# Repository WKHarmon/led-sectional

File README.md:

# LED Sectional

A WiFi-connected LED display for aviation sectional maps that shows real-time flight conditions at airports using color-coded LEDs.

## What It Does

The LED Sectional automatically fetches current weather data (METARs) from aviationweather.gov and displays flight conditions on your sectional map:

| Color | Meaning |
|-------|---------|
| Green | VFR - Clear skies, good visibility |
| Blue | MVFR - Marginal conditions |
| Red | IFR - Instrument conditions |
| Magenta | LIFR - Low IFR, poor conditions |
| Yellow | High Winds - VFR with winds over 25 knots |
| White Flash | Thunderstorms reported |
| Off | No data available |

Weather updates automatically every 15 minutes.

## What You Need

### Hardware

- **Controller board** - ESP8266-based (Wemos D1 Mini Lite recommended), or purchase a [pre-made kit](docs/kit.md)
- **LED string** - WS2811 or WS2812 LEDs (one per airport)
- **Power supply** - 5V DC, sized for your LED count
- **USB cable** - For initial setup (must support data, not charge-only)

### Your Map

You'll need a framed sectional chart with holes drilled at each airport location. See the [full build guide](docs/index.md) for detailed instructions on creating your map.

## Setup

### Step 1: Install the Firmware

1. Visit the [LED Sectional Configuration Tool](https://led-sectional.kyleharmon.com/configure/)
2. Connect your controller via USB
3. Click the **Firmware** tab
4. Click **Install Firmware** and follow the prompts

### Step 2: Connect to WiFi

After installing firmware, the controller needs your WiFi credentials:

1. Keep the USB cable connected
2. In the Configuration Tool, click **Connect**
3. Go to the **WiFi** tab
4. Enter your network name and password
5. Click **Save** - the device will reboot and connect

**Note:** The controller only works with 2.4 GHz WiFi networks.

### Step 3: Add Your Airports

1. In the Configuration Tool, go to the **Airports** tab
2. Add airports in order matching your LED string (LED 1 first, LED 2 second, etc.)
3. Use standard ICAO codes (e.g., KSFO, KJFK, KORD)
4. Click **Save** to upload to the device

**Special codes:**
- `NULL` - Skip an LED (leave it off)
- `VFR`, `MVFR`, `IFR`, `LIFR`, `WVFR` - Legend LEDs that always show that color
- `WBNK` - Wind blink demo - alternates between green and yellow (requires "Alternate Colors" setting enabled)

### Step 4: Mount and Enjoy

Disconnect USB, connect your 5V power supply, and mount your sectional!

## Troubleshooting

### LEDs aren't lighting up

- Check that your power supply is 5V and has enough current for your LED count
- Verify the data wire is connected to the correct pin (GPIO 14 / D5 by default)
- Make sure the LED string and controller share a common ground

### Can't connect via Web Serial

- Use Chrome, Edge, or Opera (Safari and Firefox don't support Web Serial)
- Try a different USB cable - some cables only carry power, not data
- Close any other programs that might be using the serial port

### WiFi won't connect

- Confirm your network is 2.4 GHz (5 GHz is not supported)
- Double-check the password
- Move the controller closer to your router during setup

### Some airports show no color

- The airport may not have recent METAR data
- Verify the ICAO code is correct at [aviationweather.gov](https://aviationweather.gov/)

## Adjusting Settings

In the Configuration Tool's **Settings** tab, you can adjust:

- **Brightness** - LED brightness level (0-255)
- **Wind Threshold** - Wind speed that triggers yellow color (default: 25 knots)
- **Lightning Animation** - Enable/disable flashing for thunderstorms
- **High Wind Indication** - Enable/disable yellow for high winds
- **Light Sensor** - Enable automatic brightness based on room lighting (requires additional hardware)

### Home Assistant Integration

The LED Sectional can integrate with Home Assistant for smart home control. Once configured, your sectional appears as a light in Home Assistant where you can:

- Turn the display on/off
- Adjust brightness
- Include in automations (e.g., dim at night, turn off when away)

To set up, go to **Settings > Advanced Settings** in the Configuration Tool and enable MQTT. Enter your Home Assistant's MQTT broker address and credentials. The device will automatically appear in Home Assistant via MQTT Discovery.

## More Information

- [Full Build Guide](docs/index.md) - Detailed instructions for building your sectional
- [Kit Information](docs/kit.md) - Pre-made electronics kit
- [Contributing & Development](CONTRIBUTING.md) - For developers who want to modify the code

## Acknowledgments

- Inspired by [this Reddit post](https://www.reddit.com/r/flying/comments/7avr8q/flight_conditions_sectional_wall_art_thing/) and [Dylan Rush's blog](http://blog.dylanhrush.com/2017/07/live-sectional-map.html)
- Weather data from [aviationweather.gov](https://aviationweather.gov/)
- Web flashing powered by [ESP Web Tools](https://esphome.github.io/esp-web-tools/)

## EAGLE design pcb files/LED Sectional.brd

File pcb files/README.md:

# PCB Files
Originally this project used a WEMOS D1 Mini; however, to make assembly a bit easier the PCB now has all the components placed on the PCB directly, including an ESP8285 microcontroller. All of the SMD components are from the parts library that [jlcpcb.com](https://jlcpcb.com) can assemble directly for cheap. The files in this folder are:

* LED Sectional PCB - EasyEDA.json - PCB design file for import into EasyEDA.
* LED Sectional - Gerbers.zip - PCB production files that should be usable by any PCB manufacturer.
* LED Sectional - BOM.csv - All of the components used in the board design.
* LED Sectional - Centroid.csv - Pick and place file for assembly of the SMD components.

If assembling through jlcpcb.com, it's still necessary to solder all of the through hole components like the micro USB, power, and LED connectors. Other assembly fabs can handle the thru-hole components, but most charge significantly more for the via-in-pads that are used in the design.

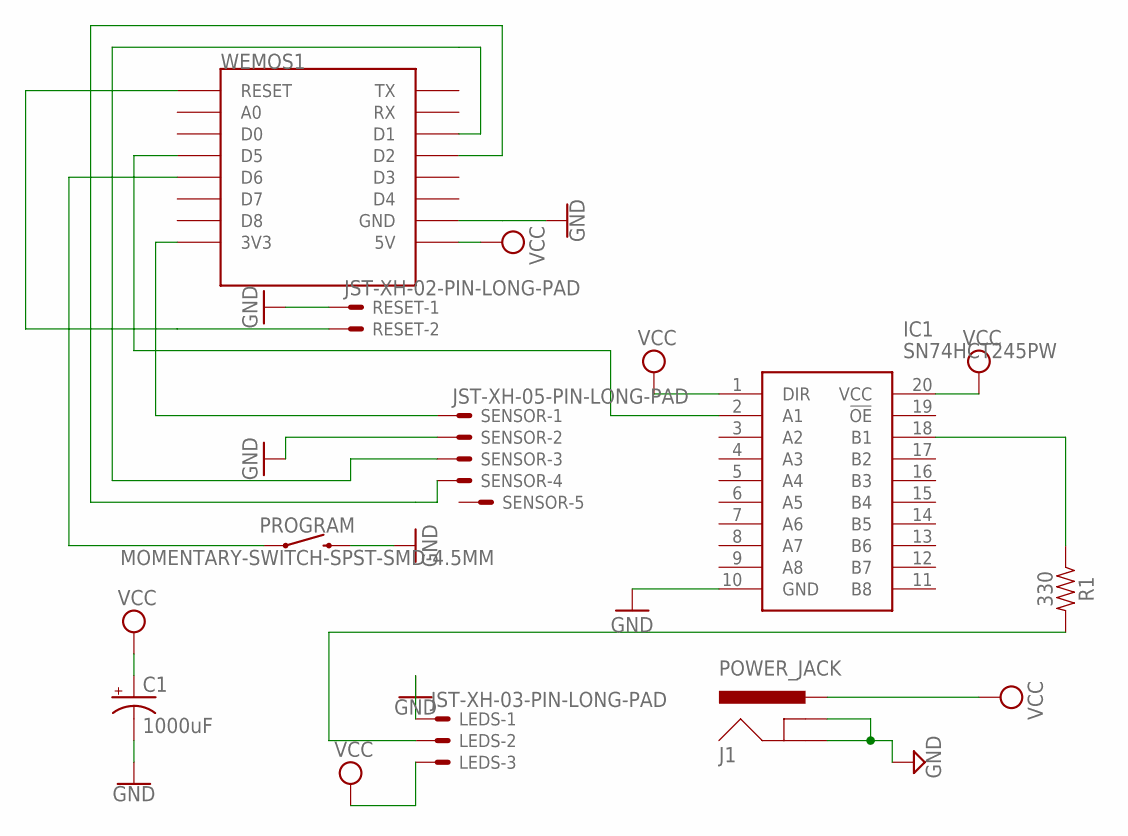
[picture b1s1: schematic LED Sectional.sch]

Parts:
C1: 1000uF; CT7343
IC1: SN74HCT245PW; SOP65P640X120-20N
J1: POWER_JACK; POWER_JACK_PTH
LEDS: JST-XH-03-PIN-LONG-PAD; JST-XH-03-PACKAGE-LONG-PAD
PROGRAM: MOMENTARY-SWITCH-SPST-SMD-4.5MM; TACTILE_SWITCH_SMD_4.5MM
R1: 330; 0603
RESET: JST-XH-02-PIN-LONG-PAD; JST-XH-02-PACKAGE-LONG-PAD
SENSOR: JST-XH-05-PIN-LONG-PAD; JST-XH-05-PACKAGE-LONG-PAD
WEMOS1: WEMOS-D1-MINI

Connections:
GND: C1.-, IC1.10 (GND), J1.GND, J1.GNDBREAK, LEDS.1, PROGRAM.1 (2), PROGRAM.4 (2), RESET.1, SENSOR.2, WEMOS1.GND
unnamed: SENSOR.1, WEMOS1.3V3
unnamed: LEDS.2, R1.2
unnamed: IC1.2 (A1), WEMOS1.D5
unnamed: IC1.18 (B1), R1.1
unnamed: SENSOR.3, WEMOS1.D1
unnamed: SENSOR.4, WEMOS1.D2
unnamed: PROGRAM.2 (1), PROGRAM.3 (1), WEMOS1.D6
unnamed: RESET.2, WEMOS1.RESET
VCC: C1.+, IC1.1 (DIR), IC1.20 (VCC), J1.PWR, LEDS.3, WEMOS1.5V

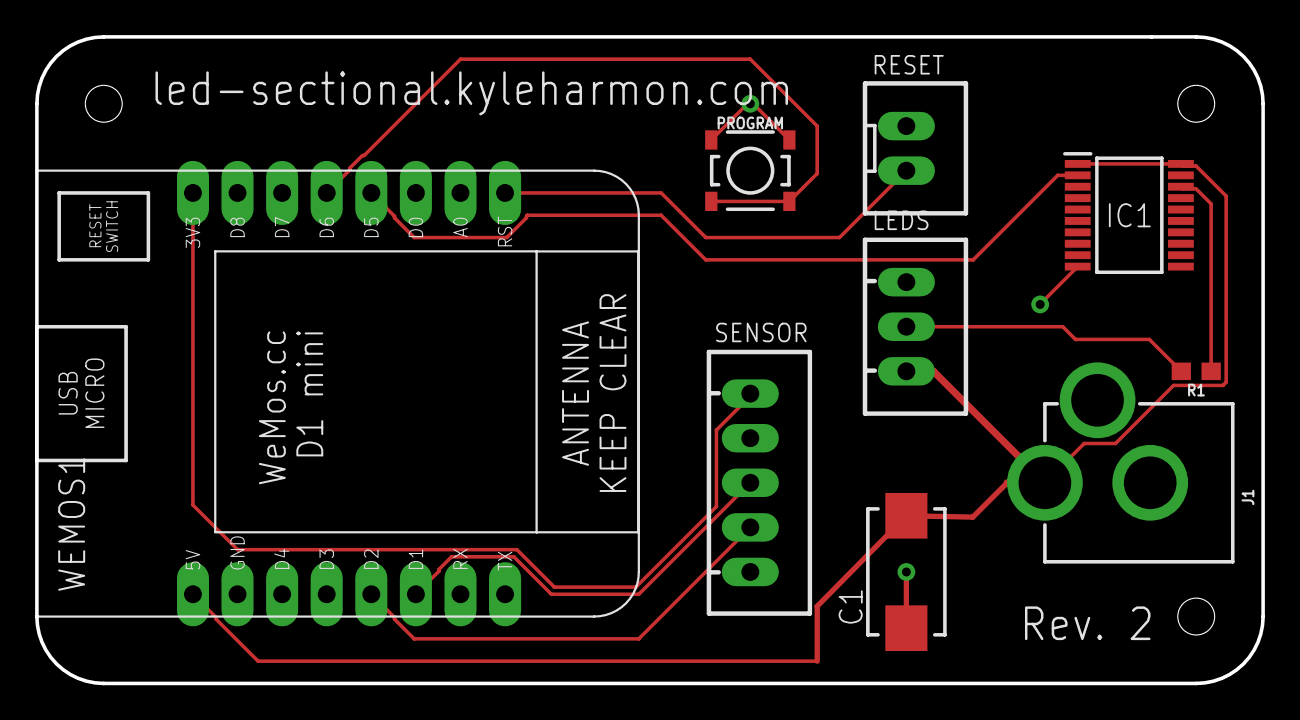
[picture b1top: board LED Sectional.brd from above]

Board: 2 copper layers, 69.8 x 36.8 mm, 9 parts (0 on the bottom side), 10 nets.

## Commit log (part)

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2018-07-23 Initial upload
2018-09-01 Updated brightness, LED order, etc.
2018-09-07 Rename to match project name
2018-09-15 Consider gusts when determining winds; adjust wind threshold to >25
2018-09-16 Set theme jekyll-theme-slate
2018-09-16 Image update
2018-09-16 Fix bullet syntax
2018-09-16 Final doc update for today
2018-09-16 Big doc update
2018-09-16 Add TOC
2018-09-16 Formatting changes
2018-09-16 TOC update
2018-09-16 Context for capacitor and resistor
2018-09-16 Docs
2018-09-18 Create CNAME
2018-09-30 LEDs for second map
2018-09-30 Update logic for key
2018-10-02 Update documentation
2018-12-15 Prevent software timeout + use BearSSL
2018-12-19 Fix documentation changes.
2018-12-23 Add PCB files
2018-12-23 More info
2018-12-26 Update links and add note about open source.
2018-12-27 Update with info on the kit
2018-12-27 Add more kit docs.
2018-12-27 Various documentation and STL updates.
2018-12-27 Updated STL file.
2019-01-02 Bug fixes
2019-01-07 Light sensor update
2019-01-08 Update sensor code.
2019-01-12 Update for digital light sensor.
2019-02-12 Update board layouts and kit information in documentation.
2019-03-05 Add support for TSL2561 digital light sensor, and move important settings to top.
2019-03-06 Fix default data pin.
2019-03-13 Allow duplicate airports.
2019-03-30 This seems to fix an issue where LED #100 wasn't getting weather applied to it
2019-04-14 Minor doc update.
2019-05-29 Add lightning delay for TSL light sensor.
2020-01-21 Update default pin; update pcb layout.
2020-04-16 Add library for encoder
2020-04-25 Fix formatting
2020-05-23 Ignore instances of "TS" before "RMK" as "TS" may appear after "RMK" meaning something other than thunderstorm.
2020-05-26 Update led-sectional.ino
    Added Wifi Manager for wireless configuration and removed hard coded wireless setup.
2020-07-04 Reduced memory usage.
2020-08-13 Just updating default airports.
2020-08-25 Image fix.
2020-08-29 Use WiFiManager rather than hard-coding creds.
2020-08-29 Don't need FS.h
2020-08-29 Decrease default brightness
2020-09-01 .ino files are easier to work with in Arduino IDE.
2020-11-20 ADDS server is rejecting requests without a UA
2021-08-23 Updated docs
2021-08-31 byte -> unsigned char
2023-05-02 Checks raw METAR for LTG in RMK
2025-09-17 New BASE_URI because of API changes
2025-09-25 Couple of additional changes I forgot to include in the last commit.
2026-04-12 Bump the all-actions group with 9 updates
    Bumps the all-actions group with 9 updates:
    | Package | From | To |
    | --- | --- | --- |
    | [actions/checkout](https://github.com/actions/checkout) | `4` | `6` |
    | [actions/setup-python](https://github.com/actions/setup-python) | `5` | `6` |
    | [actions/upload-artifact](https://github.com/actions/upload-artifact) | `4` | `7` |
2026-04-12 Bump the minor-and-patch group in /web with 4 updates
    Bumps the minor-and-patch group in /web with 4 updates: [autoprefixer](https://github.com/postcss/autoprefixer), [eslint-plugin-react-refresh](https://github.com/ArnaudBarre/eslint-plugin-react-refre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
    Updates `autoprefixer` from 10.4.23 to 10.4.27
    - [Release notes](https://github.com/postcss/autoprefixer/releases)
    - [Changelog](https://github.com/postcss/autoprefixer/blob/main/CHANGELOG.md)
    - [Commits](https://github.com/postcss/autoprefixer/compare/10.4.23...10.4.27)
    Upd
2026-04-12 Bump the major group in /web with 13 updates
    Bumps the major group in /web with 13 updates:
    | Package | From | To |
    | --- | --- | --- |
    | [@dnd-kit/sortable](https://github.com/clauderic/dnd-kit/tree/HEAD/packages/sortable) | `8.0.0` | `10.0.0` |
    | [react](https://github.com/facebook/react/tree/HEAD/packages/react) | `18.3.1` | `19.2.5` |
    | [@types/react](https://github.com/DefinitelyTyped/DefinitelyTyped/tree/HEAD/types/react) | `18.3.27` | `19.2.14` |
2026-04-12 Bump the minor-and-patch group in /web with 3 updates
    Bumps the minor-and-patch group in /web with 3 updates: [@eslint/js](https://github.com/eslint/eslint/tree/HEAD/packages/js), [eslint](https://github.com/eslint/eslint) and [typescript](https://githu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
    Updates `@eslint/js` from 9.39.2 to 9.39.4
    - [Release notes](https://github.com/eslint/eslint/releases)
    - [Commits](https://github.com/eslint/eslint/commits/v9.39.4/packages/js)
    Updates `eslint` from 9.39.2 to 9.39.4
    - [Release notes](https://github.com/eslint/eslint/releases)
2026-04-12 Bump the minor-and-patch group in /web with 3 updates (#46)
    Bumps the minor-and-patch group in /web with 3 updates: [@eslint/js](https://github.com/eslint/eslint/tree/HEAD/packages/js), [eslint](https://github.com/eslint/eslint) and [typescript](https://githu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
    Updates `@eslint/js` from 9.39.2 to 9.39.4
    - [Release notes](https://github.com/eslint/eslint/releases)
    - [Commits](https://github.com/eslint/eslint/commits/v9.39.4/packages/js)
    Updates `eslint` from 9.39.2 to 9.39.4
    - [Release notes](https://github.com/eslint/eslint/releases)
2026-04-19 Bump the minor-and-patch group in /web with 3 updates
    Bumps the minor-and-patch group in /web with 3 updates: [autoprefixer](https://github.com/postcss/autoprefixer), [postcss](https://github.com/postcss/postcss) and [typescript-eslint](https://github.c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
    Updates `autoprefixer` from 10.4.27 to 10.5.0
    - [Release notes](https://github.com/postcss/autoprefixer/releases)
    - [Changelog](https://github.com/postcss/autoprefixer/blob/main/CHANGELOG.md)
    - [Commits](https://github.com/postcss/autoprefixer/compare/10.4.27...10.5.0)
    Updates `postcss` from 8.5.9 to 8.5.10
2026-04-19 Bump the minor-and-patch group in /web with 3 updates (#48)
    Bumps the minor-and-patch group in /web with 3 updates: [autoprefixer](https://github.com/postcss/autoprefixer), [postcss](https://github.com/postcss/postcss) and [typescript-eslint](https://github.c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
    Updates `autoprefixer` from 10.4.27 to 10.5.0
    - [Release notes](https://github.com/postcss/autoprefixer/releases)
    - [Changelog](https://github.com/postcss/autoprefixer/blob/main/CHANGELOG.md)
    - [Commits](https://github.com/postcss/autoprefixer/compare/10.4.27...10.5.0)
    Updates `postcss` from 8.5.9 to 8.5.10
2026-04-26 Bump typescript-eslint in /web in the minor-and-patch group (#49)
    Bumps the minor-and-patch group in /web with 1 update: [typescript-eslint](https://github.com/typescript-eslint/typescript-eslint/tree/HEAD/packages/typescript-eslint).
    Updates `typescript-eslint` from 8.58.2 to 8.59.0
    - [Release notes](https://github.com/typescript-eslint/typescript-eslint/releases)
    - [Changelog](https://github.com/typescript-eslint/typescript-eslint/blob/main/packages/typescript-eslint/CHANGELOG.md)
    - [Commits](https://github.com/typescript-eslint/typescript-eslint/commits/v8.59.0/packages/typescript-eslint)
    ---
2026-05-03 Bump the minor-and-patch group in /web with 2 updates (#50)
    Bumps the minor-and-patch group in /web with 2 updates: [postcss](https://github.com/postcss/postcss) and [typescript-eslint](https://github.com/typescript-eslint/typescript-eslint/tree/HEAD/packages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
    Updates `postcss` from 8.5.10 to 8.5.13
    - [Release notes](https://github.com/postcss/postcss/releases)
    - [Changelog](https://github.com/postcss/postcss/blob/main/CHANGELOG.md)
    - [Commits](https://github.com/postcss/postcss/compare/8.5.10...8.5.13)
    Updates `typescript-eslint` from 8.59.0 to 8.59.1
2026-05-10 Bump the minor-and-patch group in /web with 2 updates (#51)
    Bumps the minor-and-patch group in /web with 2 updates: [postcss](https://github.com/postcss/postcss) and [typescript-eslint](https://github.com/typescript-eslint/typescript-eslint/tree/HEAD/packages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
    Updates `postcss` from 8.5.13 to 8.5.14
    - [Release notes](https://github.com/postcss/postcss/releases)
    - [Changelog](https://github.com/postcss/postcss/blob/main/CHANGELOG.md)
    - [Commits](https://github.com/postcss/postcss/compare/8.5.13...8.5.14)
    Updates `typescript-eslint` from 8.59.1 to 8.59.2
2026-05-17 Bump typescript-eslint in /web in the minor-and-patch group (#52)
    Bumps the minor-and-patch group in /web with 1 update: [typescript-eslint](https://github.com/typescript-eslint/typescript-eslint/tree/HEAD/packages/typescript-eslint).
    Updates `typescript-eslint` from 8.59.2 to 8.59.3
    - [Release notes](https://github.com/typescript-eslint/typescript-eslint/releases)
    - [Changelog](https://github.com/typescript-eslint/typescript-eslint/blob/main/packages/typescript-eslint/CHANGELOG.md)
    - [Commits](https://github.com/typescript-eslint/typescript-eslint/commits/v8.59.3/packages/typescript-eslint)
    ---
2026-05-24 Bump the minor-and-patch group in /web with 2 updates (#53)
    Bumps the minor-and-patch group in /web with 2 updates: [postcss](https://github.com/postcss/postcss) and [typescript-eslint](https://github.com/typescript-eslint/typescript-eslint/tree/HEAD/packages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
    Updates `postcss` from 8.5.14 to 8.5.15
    - [Release notes](https://github.com/postcss/postcss/releases)
    - [Changelog](https://github.com/postcss/postcss/blob/main/CHANGELOG.md)
    - [Commits](https://github.com/postcss/postcss/compare/8.5.14...8.5.15)
    Updates `typescript-eslint` from 8.59.3 to 8.59.4
2026-05-31 Bump typescript-eslint in /web in the minor-and-patch group (#55)
    Bumps the minor-and-patch group in /web with 1 update: [typescript-eslint](https://github.com/typescript-eslint/typescript-eslint/tree/HEAD/packages/typescript-eslint).
    Updates `typescript-eslint` from 8.59.4 to 8.60.0
    - [Release notes](https://github.com/typescript-eslint/typescript-eslint/releases)
    - [Changelog](https://github.com/typescript-eslint/typescript-eslint/blob/main/packages/typescript-eslint/CHANGELOG.md)
    - [Commits](https://github.com/typescript-eslint/typescript-eslint/commits/v8.60.0/packages/typescript-eslint)
    ---
2026-06-07 Bump the minor-and-patch group in /web with 2 updates
    Bumps the minor-and-patch group in /web with 2 updates: [typescript-eslint](https://github.com/typescript-eslint/typescript-eslint/tree/HEAD/packages/typescript-eslint) and [vite](https://github.com/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
    Updates `typescript-eslint` from 8.60.0 to 8.60.1
    - [Release notes](https://github.com/typescript-eslint/typescript-eslint/releases)
    - [Changelog](https://github.com/typescript-eslint/typescript-eslint/blob/main/packages/typescript-eslint/CHANGELOG.md)
    - [Commits](https://github.com/typescript-eslint/typescript-eslint/commits/v8.60.1/packages/typescript-eslint)
    Updates `vite` from 6.4.2 to 6.4.3
2026-06-14 Bump typescript-eslint in /web in the minor-and-patch group
    Bumps the minor-and-patch group in /web with 1 update: [typescript-eslint](https://github.com/typescript-eslint/typescript-eslint/tree/HEAD/packages/typescript-eslint).
    Updates `typescript-eslint` from 8.60.1 to 8.61.0
    - [Release notes](https://github.com/typescript-eslint/typescript-eslint/releases)
    - [Changelog](https://github.com/typescript-eslint/typescript-eslint/blob/main/packages/typescript-eslint/CHANGELOG.md)
    - [Commits](https://github.com/typescript-eslint/typescript-eslint/commits/v8.61.0/packages/typescript-eslint)
    ---
2026-06-21 Bump actions/checkout from 6 to 7 in the all-actions group
    Bumps the all-actions group with 1 update: [actions/checkout](https://github.com/actions/checkout).
    Updates `actions/checkout` from 6 to 7
    - [Release notes](https://github.com/actions/checkout/releases)
    - [Changelog](https://github.com/actions/checkout/blob/main/CHANGELOG.md)
    - [Commits](https://github.com/actions/checkout/compare/v6...v7)
    ---

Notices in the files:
parts and their libraries:
SparkFun-Resistors: Licensing: Creative Commons ShareAlike 4.0 International - https://creativecommons.org/licenses/by-sa/4.0
